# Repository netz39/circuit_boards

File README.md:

Circuit Boards
==============

Various PCBs without own projects. In fact these are some circuit boards for various uses but without the usual project stuff around, just the schematics and board files and the basic stuff to get it running, that's it.

Each project is in a subfolder and has its own LICENSE and README files. If you want more information about a project, see those files.

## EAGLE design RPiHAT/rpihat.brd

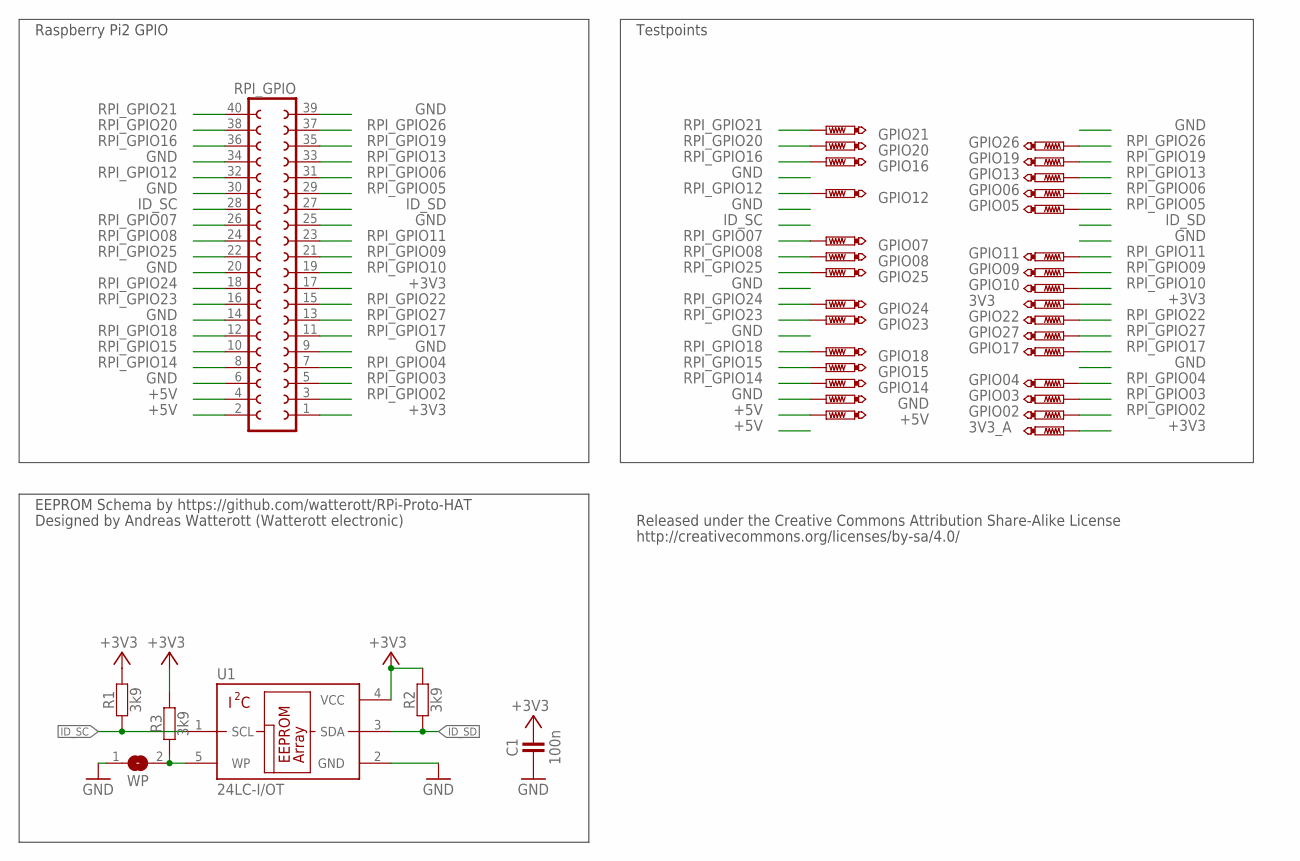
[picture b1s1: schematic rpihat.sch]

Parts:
3V3, 3V3_A: +3.3V; TP06R
+5V: PTR1TP06R; TP06R
C1: 100n; R0603
GND: PTR1TP06R; TP06R
GPIO02, GPIO03, GPIO04, GPIO05, GPIO06, GPIO07, GPIO08, GPIO09, GPIO10, GPIO11, GPIO12, GPIO13, GPIO14, GPIO15, GPIO16, GPIO17, GPIO18, GPIO19, GPIO20, GPIO21, GPIO22, GPIO23, GPIO24, GPIO25, GPIO26, GPIO27: PTR1TP06R; TP06R
R1, R2, R3: 3k9; R0603
RPI_GPIO: FE20-2
U1: 24LC-I/OT; SOT23-5
WP: JUMPER2-NOCREAM; JUMPER2_NC

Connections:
+3V3: 3V3.TP, 3V3_A.TP, C1.2, R1.2, R2.2, R3.2, RPI_GPIO.1, RPI_GPIO.17, U1.4 (VCC)
+5V: +5V.TP, RPI_GPIO.2, RPI_GPIO.4
GND: C1.1, GND.TP, RPI_GPIO.6, RPI_GPIO.9, RPI_GPIO.14, RPI_GPIO.20, RPI_GPIO.25, RPI_GPIO.30, RPI_GPIO.34, RPI_GPIO.39, U1.2 (GND), WP.1
ID_SC: R1.1, RPI_GPIO.28, U1.1 (SCL)
ID_SD: R2.1, RPI_GPIO.27, U1.3 (SDA)
RPI_GPIO02: GPIO02.TP, RPI_GPIO.3
RPI_GPIO03: GPIO03.TP, RPI_GPIO.5
RPI_GPIO04: GPIO04.TP, RPI_GPIO.7
RPI_GPIO05: GPIO05.TP, RPI_GPIO.29
RPI_GPIO06: GPIO06.TP, RPI_GPIO.31
RPI_GPIO07: GPIO07.TP, RPI_GPIO.26
RPI_GPIO08: GPIO08.TP, RPI_GPIO.24
RPI_GPIO09: GPIO09.TP, RPI_GPIO.21
RPI_GPIO10: GPIO10.TP, RPI_GPIO.19
RPI_GPIO11: GPIO11.TP, RPI_GPIO.23
RPI_GPIO12: GPIO12.TP, RPI_GPIO.32
RPI_GPIO13: GPIO13.TP, RPI_GPIO.33
RPI_GPIO14: GPIO14.TP, RPI_GPIO.8
RPI_GPIO15: GPIO15.TP, RPI_GPIO.10
RPI_GPIO16: GPIO16.TP, RPI_GPIO.36
RPI_GPIO17: GPIO17.TP, RPI_GPIO.11
RPI_GPIO18: GPIO18.TP, RPI_GPIO.12
RPI_GPIO19: GPIO19.TP, RPI_GPIO.35
RPI_GPIO20: GPIO20.TP, RPI_GPIO.38
RPI_GPIO21: GPIO21.TP, RPI_GPIO.40
RPI_GPIO22: GPIO22.TP, RPI_GPIO.15
RPI_GPIO23: GPIO23.TP, RPI_GPIO.16
RPI_GPIO24: GPIO24.TP, RPI_GPIO.18
RPI_GPIO25: GPIO25.TP, RPI_GPIO.22
RPI_GPIO26: GPIO26.TP, RPI_GPIO.37
RPI_GPIO27: GPIO27.TP, RPI_GPIO.13
WP: R3.1, U1.5 (WP), WP.2

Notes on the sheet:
EEPROM Schema by https://github.com/watterott/RPi-Proto-HAT
Raspberry Pi2 GPIO
Testpoints
Designed by Andreas Watterott (Watterott electronic)
http://creativecommons.org/licenses/by-sa/4.0/
Released under the Creative Commons Attribution Share-Alike License

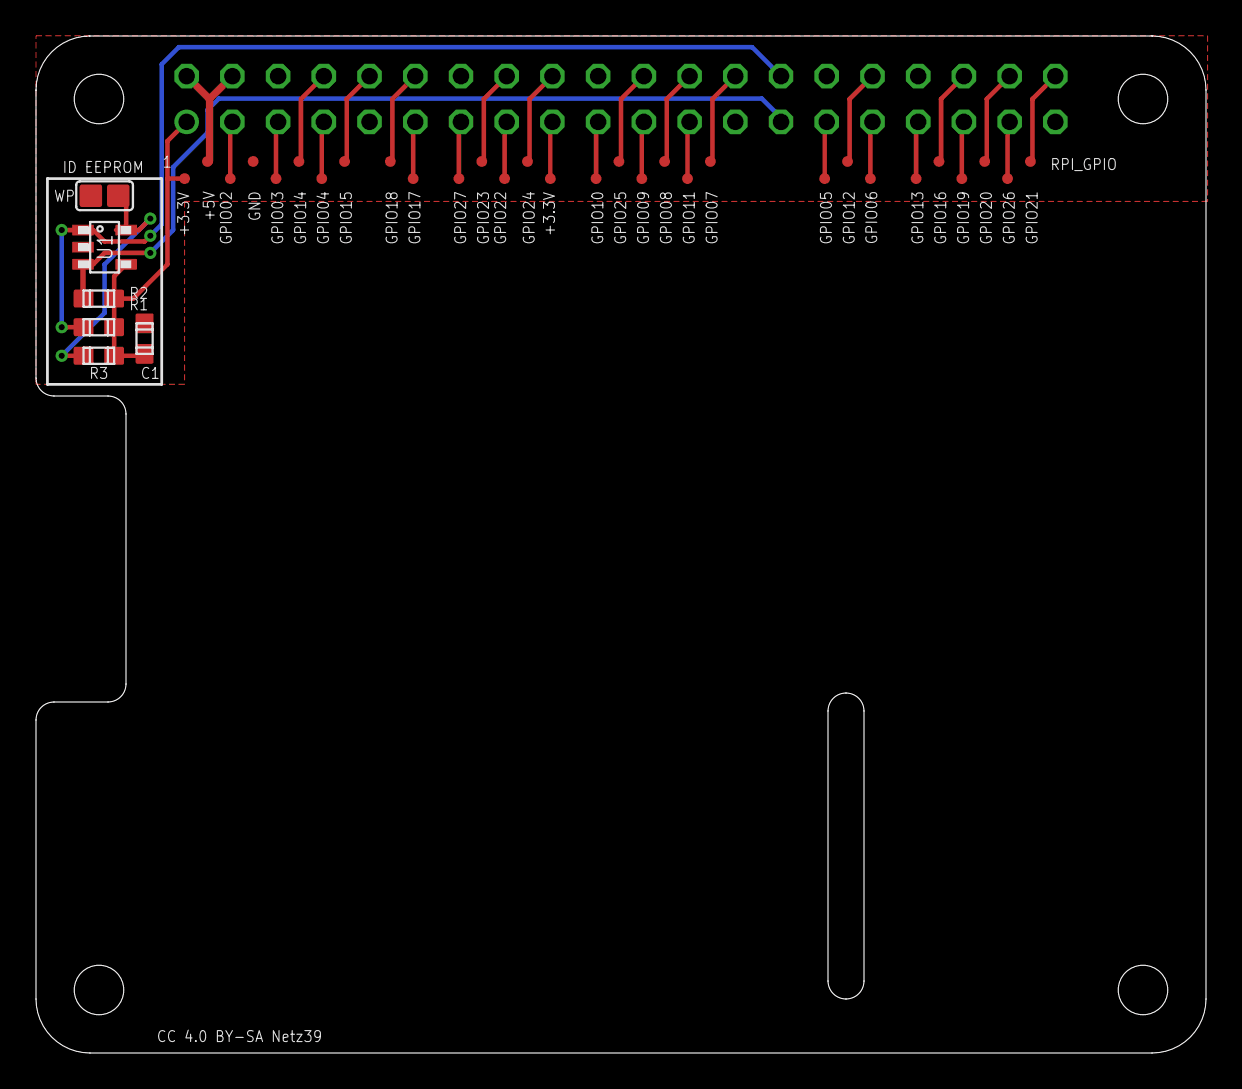
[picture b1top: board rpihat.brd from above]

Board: 2 copper layers, 65.0 x 56.5 mm, 37 parts (1 on the bottom side), 32 nets.

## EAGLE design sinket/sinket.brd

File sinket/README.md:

The [Trinket](http://learn.adafruit.com/introducing-trinket) by adafruit
is an awesome small board based on an Atmel ATtiny85 microcontroller.
Although just a little less than 8$ or 8€ we made a clone for ourselves
which is not that small but a single layer PCB design for easy
manufacturing in your local hackerspace, of course 100% compatible on
the electrical side. You can use all the software, tutorials and so on.
The parts are easily available in Europe or just right already there in
your part storage.

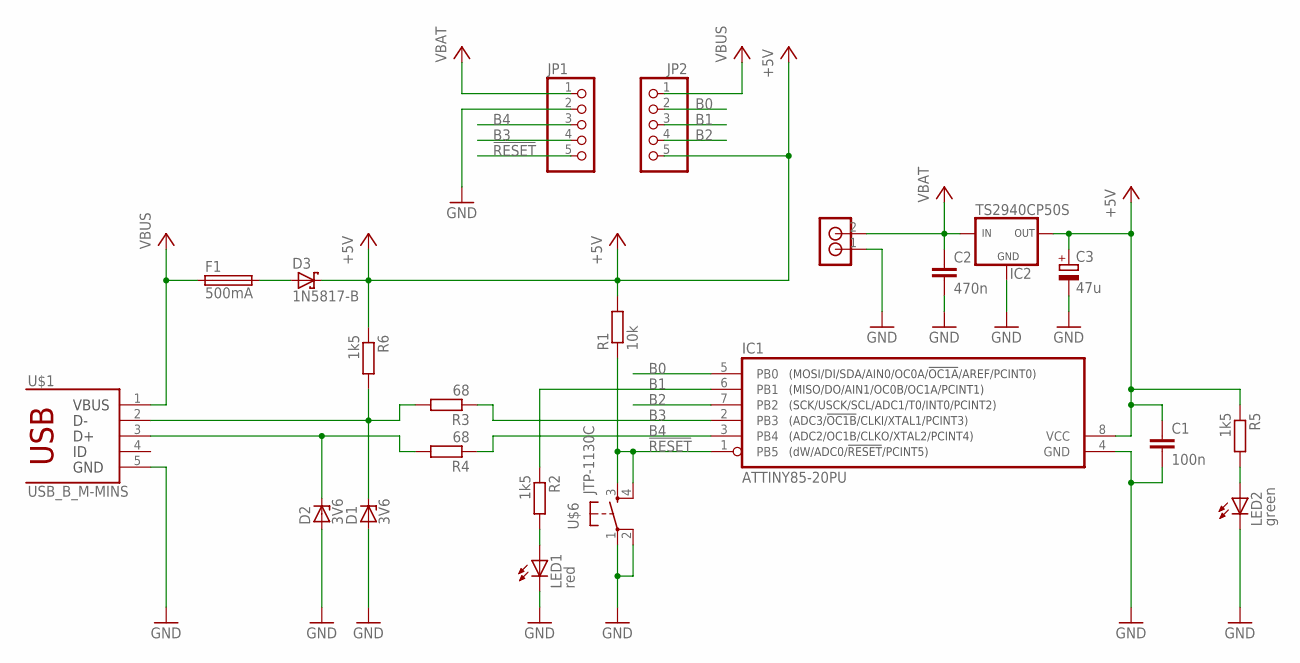
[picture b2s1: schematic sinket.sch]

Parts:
C1: 100n; C1206
C2: 470n; C025-030X050
C3: 47u; E2,5-6
D1, D2: 3V6; SOD80C
D3: 1N5817-B; DO41-7.6
F1: 500mA; LP60-050
IC1: ATTINY85-20PU; 8P3
IC2: TS2940CP50S; TO-252
JP1, JP2: PINHD-1X5; 1X05
LED1: red; LED5MM
LED2: green; LED5MM
R1: 10k; R1206
R2, R5, R6: 1k5; R1206
R3, R4: 68; R1206
U$1: USB_B_M-MINS; LUMBERG_2486-01
U$6: JTP-1130C; JTP-1130
U$7: RIACON_101_2

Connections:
!RESET: IC1.1 (PB5), JP1.5, R1.1, U$6.3 (S), U$6.4 (S1)
+5V: C1.1, C3.+, D3.C, IC1.8 (VCC), IC2.3 (OUT), JP2.5, R1.2, R5.1, R6.1
B0: IC1.5 (PB0), JP2.2
B1: IC1.6 (PB1), JP2.3, R2.1
B2: IC1.7 (PB2), JP2.4
B3: IC1.2 (PB3), JP1.4, R3.1
B4: IC1.3 (PB4), JP1.3, R4.1
GND: C1.2, C2.2, C3.-, D1.A, D2.A, IC1.4 (GND), IC2.2 (GND), JP1.2, LED1.K (C), LED2.K (C), U$1.5, U$6.1, U$6.2 (P1), U$7.1
unnamed: D1.C, R3.2, R6.2, U$1.2
unnamed: D3.A, F1.P$2 (2)
unnamed: D2.C, R4.2, U$1.3
unnamed: LED1.A, R2.2
unnamed: LED2.A, R5.2
VBAT: C2.1, IC2.1 (IN), JP1.1, U$7.2
VBUS: F1.P$1 (1), JP2.1, U$1.1

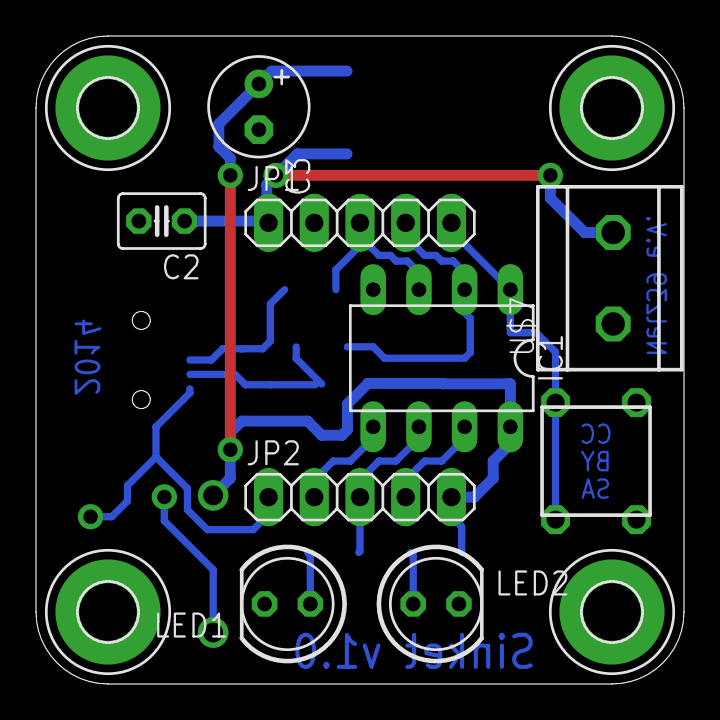
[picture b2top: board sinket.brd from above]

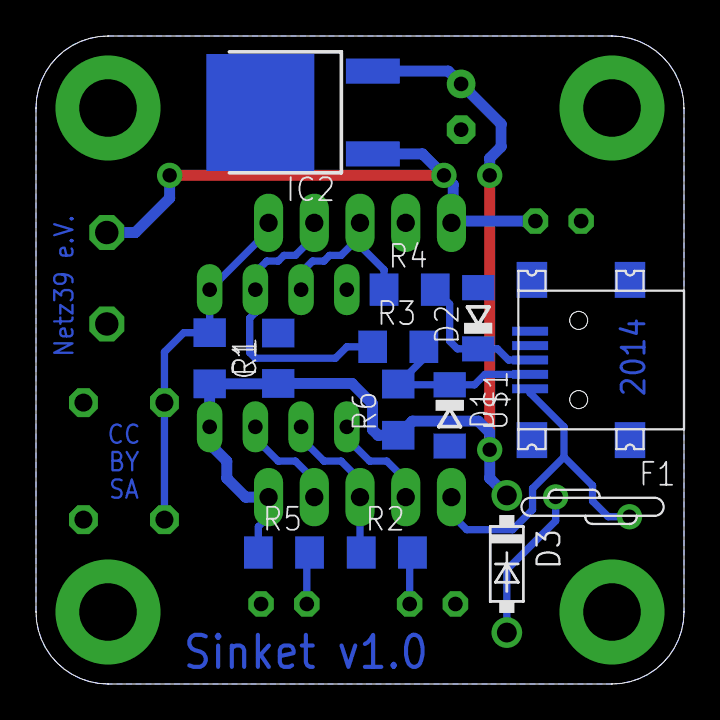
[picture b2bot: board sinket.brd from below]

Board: 2 copper layers, 36.0 x 36.0 mm, 26 parts (13 on the bottom side), 15 nets.

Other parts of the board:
U$2, U$3, U$4, U$5: 3,2-PAD

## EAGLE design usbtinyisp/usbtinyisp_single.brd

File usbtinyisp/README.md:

This is the circuit and layout for an AVR programmer and SPI interface. It's based on USBtinyISP from [adafruit](http://learn.adafruit.com/usbtinyisp) and you should flash their firmware, because it's also using their USB id. ;-)

However this is a single layer PCB with another form factor. We made this in our Hackerspace [Netz39](http://www.netz39.de/) for the AVR101 and other courses people can attend there.

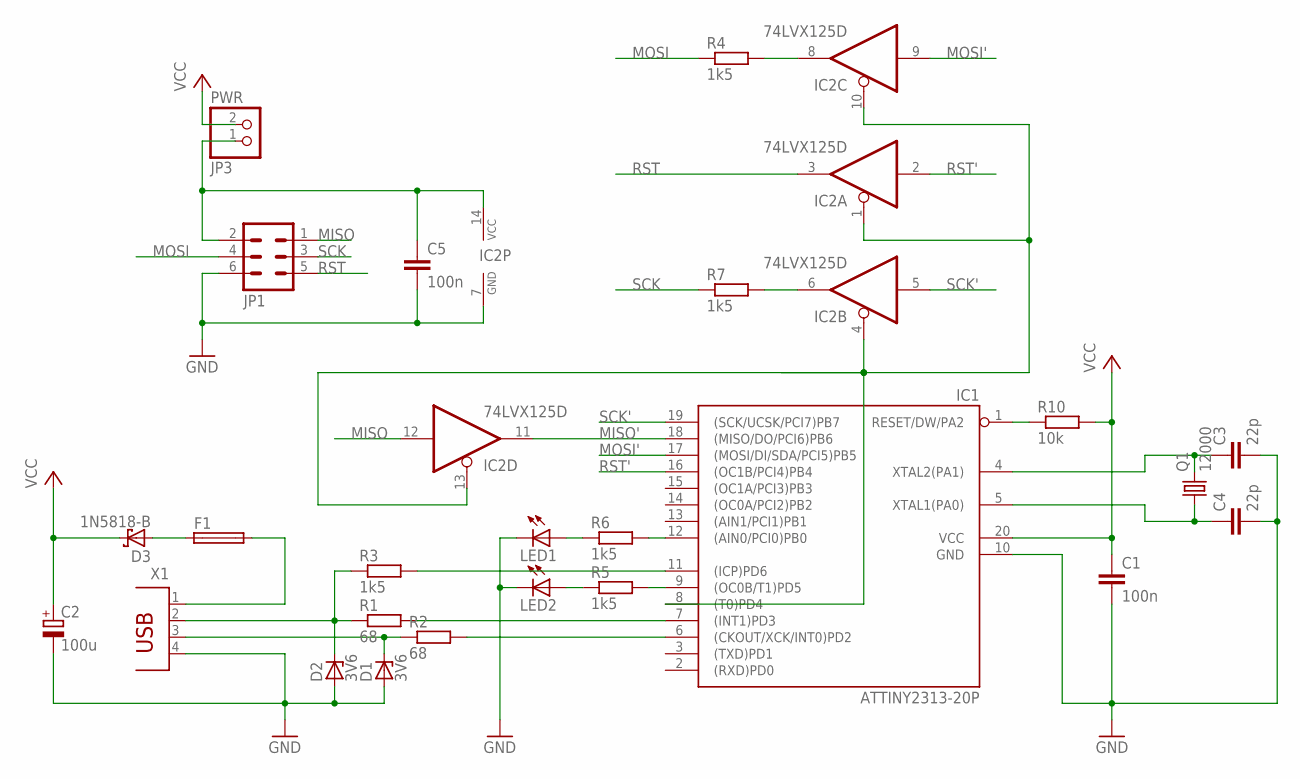
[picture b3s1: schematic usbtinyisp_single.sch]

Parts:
C1, C5: 100n; C0805
C2: 100u; E2,5-6
C3, C4: 22p; C1206
D1, D2: 3V6; SOD80C
D3: 1N5818-B; DO41-7.6
F1: PTC-FUSE-LP60-050; LP60-050
IC1: ATTINY2313-20P; DIL20
IC2: 74LVX125D; SO14
JP1: ML6
JP3: PWR; 1X02
LED1, LED2: LED3MM
Q1: 12000; HC49U-V
R1, R2: 68; 0207/10
R3, R4, R5, R6: 1k5; R0805
R7: 1k5; 0207/10
R10: 10k; R0805
X1: PN61729

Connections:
GND: C1.2, C2.-, C3.2, C4.2, C5.2, D1.A, D2.A, IC1.10 (GND), IC2.7 (GND), JP1.6, LED1.K (C), LED2.K (C), X1.4
MISO: IC2.12 (I), JP1.1
MISO': IC1.18 ((MISO/DO/PCI6)PB6), IC2.11 (O)
MOSI: JP1.4, R4.1
MOSI': IC1.17 ((MOSI/DI/SDA/PCI5)PB5), IC2.9 (I)
unnamed: D2.C, R1.1, R3.1, X1.2
unnamed: D1.C, R2.1, X1.3
unnamed: IC1.7 ((INT1)PD3), R1.2
unnamed: LED1.A, R6.1
unnamed: IC1.6 ((CKOUT/XCK/INT0)PD2), R2.2
unnamed: IC1.12 ((AIN0/PCI0)PB0), R6.2
unnamed: IC1.1 (RESET/DW/PA2), R10.1
unnamed: IC1.9 ((OC0B/T1)PD5), R5.2
unnamed: LED2.A, R5.1
unnamed: IC2.6 (O), R7.2
unnamed: IC2.8 (O), R4.2
unnamed: D3.A, F1.P$1 (1)
unnamed: IC1.8 ((T0)PD4), IC2.1 (OE), IC2.4 (OE), IC2.10 (OE), IC2.13 (OE)
unnamed: IC1.11 ((ICP)PD6), R3.2
RST: IC2.3 (O), JP1.5
RST': IC1.16 ((OC1B/PCI4)PB4), IC2.2 (I)
SCK: JP1.3, R7.1
SCK': IC1.19 ((SCK/UCSK/PCI7)PB7), IC2.5 (I)
VBUS: F1.P$2 (2), X1.1
VCC: C1.1, C2.+, D3.C, IC1.20 (VCC), JP3.2, R10.2
VTARGET: C5.1, IC2.14 (VCC), JP1.2, JP3.1
XTAL1: C4.1, IC1.5 (XTAL1(PA0)), Q1.1
XTAL2: C3.1, IC1.4 (XTAL2(PA1)), Q1.2

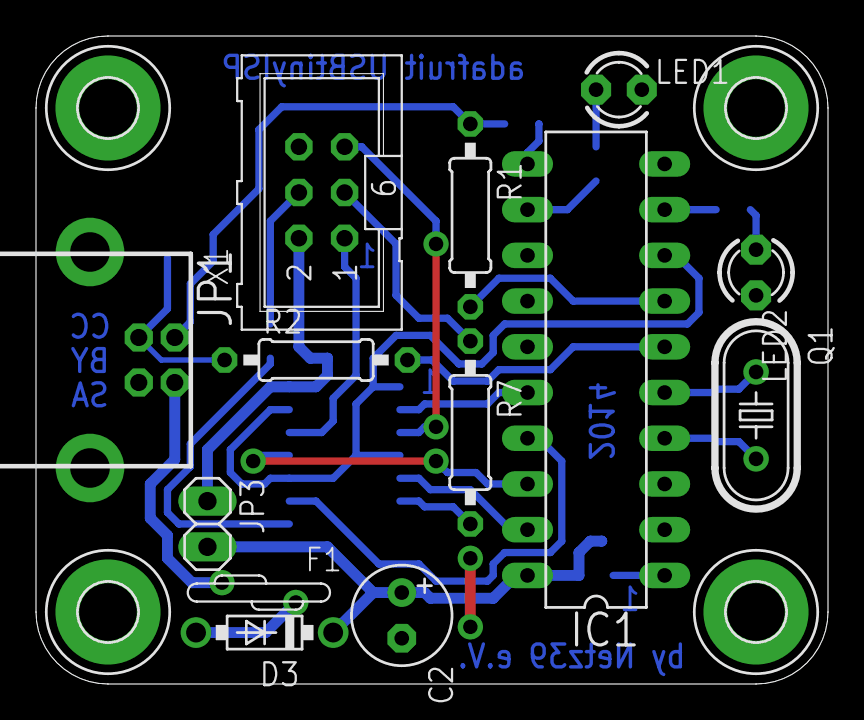
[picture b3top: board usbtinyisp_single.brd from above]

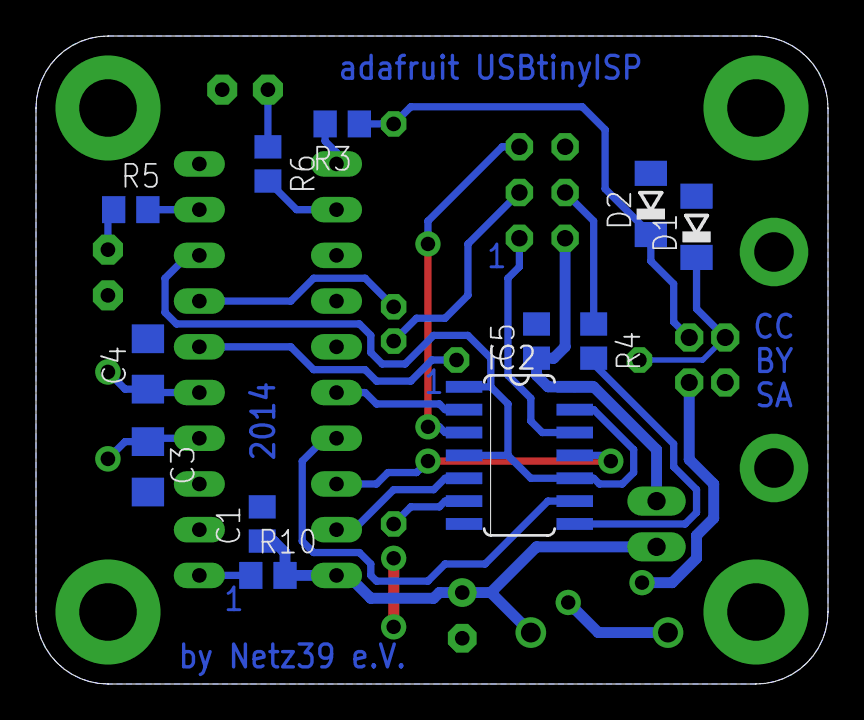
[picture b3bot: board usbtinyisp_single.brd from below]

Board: 2 copper layers, 44.0 x 36.0 mm, 29 parts (12 on the bottom side), 28 nets.

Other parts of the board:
U$1, U$2, U$3, U$4: 3,2-PAD

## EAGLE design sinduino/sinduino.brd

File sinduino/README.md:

This is yet another [Arduino](http://arduino.cc/) clone. It's based on the [Paperduino Leonardo](http://txapuzas.blogspot.de/2009/12/paperduino-leonardo-clon-de-arduino.html), but it's called *sinduino*. The name comes from the purpose of this board to create a single layer Arduino clone and the usual "duino".

As said above we want a single layer PCB to be able to etch it without all the problems a dual layer etching at home has. There are single layer Arduino boards out there, but none of them has USB. To simplify the design and staying low cost we wanted to use the ATmega32U4 with integrated USB which is the one used on the Arduino Leonardo, too.

However there are some trade offs. The most important one: this is not pin compatible to the well known Arduino and its shields

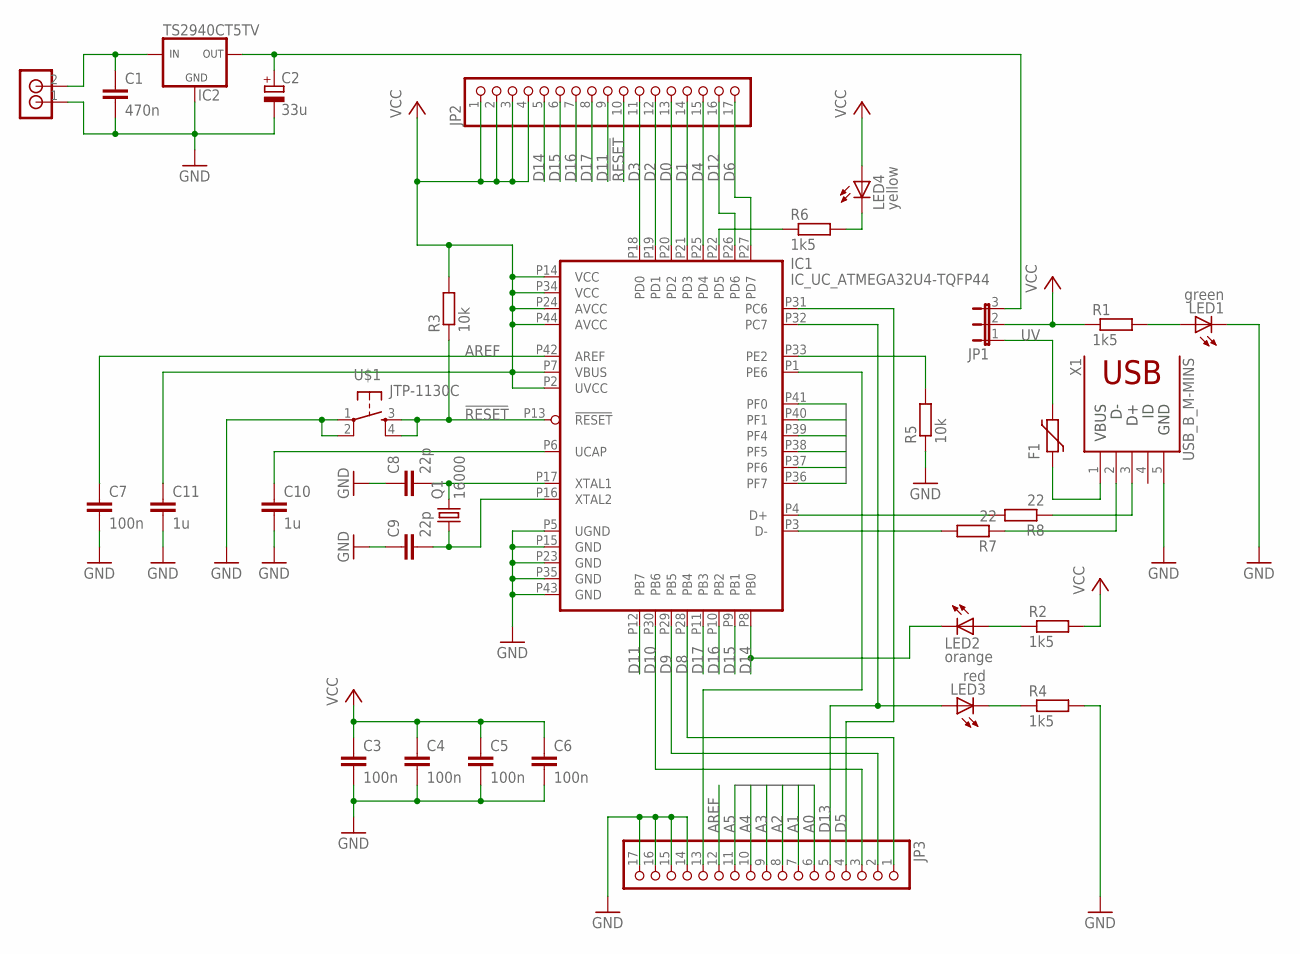
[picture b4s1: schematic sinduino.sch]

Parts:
C1: 470n; C025-025X050
C2: 33u; E2,5-5
C3, C4, C5, C6, C7: 100n; C1206
C8, C9: 22p; C1206
C10, C11: 1u; C1206
F1: FUSE_PTC-1812; PTC1812L
IC1: IC_UC_ATMEGA32U4-TQFP44; TQFP-44
IC2: TS2940CT5TV; TO220V
JP1: JP2E; JP2
JP2, JP3: PINHD-1X17; 1X17
LED1: green; LED3MM
LED2: orange; LED3MM
LED3: red; LED3MM
LED4: yellow; LED3MM
Q1: 16000; HC49U-V
R1, R2, R4, R6: 1k5; R1206
R3, R5: 10k; R1206
R7, R8: 22; R1206
U$1: JTP-1130C; JTP-1130
U$3: RIACON_101_2
X1: USB_B_M-MINS; LUMBERG_2486-01

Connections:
!RESET: IC1.P13 (!RESET), JP2.10, R3.1, U$1.3 (S), U$1.4 (S1)
A0: IC1.P36 (PF7), JP3.6
A1: IC1.P37 (PF6), JP3.7
A2: IC1.P38 (PF5), JP3.8
A3: IC1.P39 (PF4), JP3.9
A4: IC1.P40 (PF1), JP3.10
A5: IC1.P41 (PF0), JP3.11
AREF: C7.1, IC1.P42 (AREF), JP3.12
D0: IC1.P20 (PD2), JP2.13
D1: IC1.P21 (PD3), JP2.14
D2: IC1.P19 (PD1), JP2.12
D3: IC1.P18 (PD0), JP2.11
D4: IC1.P25 (PD4), JP2.15
D5: IC1.P31 (PC6), JP3.4
D6: IC1.P27 (PD7), JP2.17
D7: IC1.P1 (PE6), JP3.13
D8: IC1.P28 (PB4), JP3.1
D9: IC1.P29 (PB5), JP3.2
D10: IC1.P30 (PB6), JP3.3
D11: IC1.P12 (PB7), JP2.9
D12: IC1.P26 (PD6), JP2.16
D13: IC1.P32 (PC7), JP3.5, LED3.A
D14: IC1.P8 (PB0), JP2.5, LED2.K (C)
D15: IC1.P9 (PB1), JP2.6
D16: IC1.P10 (PB2), JP2.7
D17: IC1.P11 (PB3), JP2.8
D+: IC1.P4 (D+), R8.2
D-: IC1.P3 (D-), R7.2
GND: C1.2, C2.-, C3.2, C4.2, C5.2, C6.2, C7.2, C8.1, C9.1, C10.2, C11.2, IC1.P5 (UGND), IC1.P15 (GND), IC1.P23 (GND), IC1.P35 (GND), IC1.P43 (GND), IC2.2 (GND), JP3.14, JP3.15, JP3.16, JP3.17, LED1.K (C), R4.2, R5.1, U$1.1, U$1.2 (P1), U$3.1, X1.5
HWB: IC1.P33 (PE2), R5.2
unnamed: R7.1, X1.2
unnamed: R8.1, X1.3
unnamed: F1.1, X1.1
unnamed: LED4.K (C), R6.2
unnamed: LED1.A, R1.2
unnamed: C1.1, IC2.1 (IN), U$3.2
unnamed: C2.+, IC2.3 (OUT), JP1.3
unnamed: LED2.A, R2.1
unnamed: LED3.K (C), R4.1
TXLED: IC1.P22 (PD5), R6.1
UCAP: C10.1, IC1.P6 (UCAP)
UV: F1.2, JP1.1
VCC: C3.1, C4.1, C5.1, C6.1, C11.1, IC1.P2 (UVCC), IC1.P7 (VBUS), IC1.P14 (VCC), IC1.P24 (AVCC), IC1.P34 (VCC), IC1.P44 (AVCC), JP1.2, JP2.1, JP2.2, JP2.3, JP2.4, LED4.A, R1.1, R2.2, R3.2
XTAL1: C8.2, IC1.P17 (XTAL1), Q1.2
XTAL2: C9.2, IC1.P16 (XTAL2), Q1.1

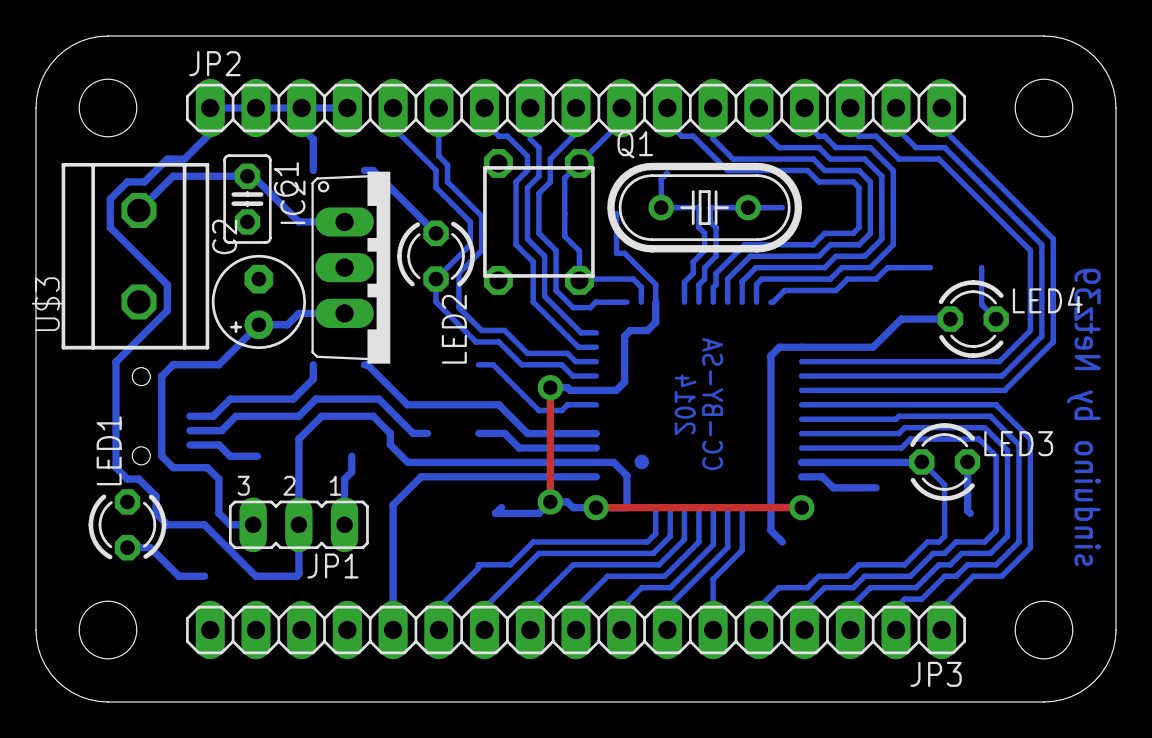
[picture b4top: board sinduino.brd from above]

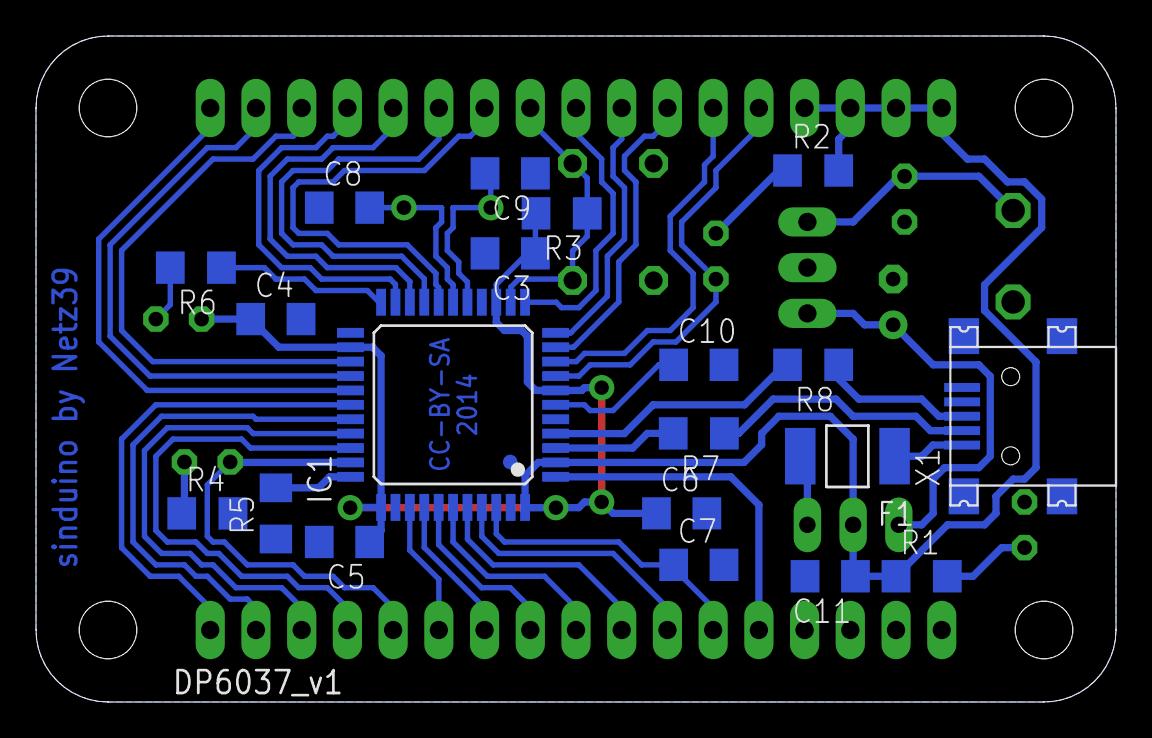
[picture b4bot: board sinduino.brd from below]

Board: 2 copper layers, 60.0 x 37.0 mm, 34 parts (20 on the bottom side), 45 nets.

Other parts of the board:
U$2: DP6037_V1

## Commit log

2014-01-10 add old v2.0 from adafruit
2014-01-10 started reworking for single layer board
2014-01-10 update dimensions and change some packages
2014-01-10 unsmash
2014-01-13 vergessene Änderungen
    wenn man nicht alles gleich commited :-/
2014-01-13 move mounting holes inward
2014-01-13 replace mounting pads
2014-01-13 swapped some gates and moved all parts around
2014-01-14 routed
    ready for soldering (first test)
2014-01-14 add text, license, and readme
2014-01-14 swap LED1 with resistor
2014-01-16 import sinduino last state
    based on [Paperduino
    Leonardo](http://txapuzas.blogspot.de/2009/12/paperduino-leonardo-clon-de-arduino.html)
2014-01-16 add license and readme
2014-01-16 proceed connecting
2014-01-17 add git ignore list
2014-01-17 almost connected everything
2014-01-18 complete schematic and start routing
2014-01-19 proceed routing, move uC, start over …
2014-01-19 switched one led with its resistor
2014-01-19 proceed routing
2014-01-19 route lower right part
2014-01-20 route left part of the board
2014-01-20 move some things around in the upper right
2014-01-20 routed all the stuff around the xtal
2014-01-20 routing complete
2014-01-20 dimension
2014-01-20 added text
2014-01-21 name some unnamed signals
    and improve xtal routing
2014-01-22 adapt resistor values and move one via
2014-02-17 replace mini usb connector and fix #3
2014-02-20 change XTAL capicator values to 22p (you can not buy 18p)
2014-02-28 move vias for round wire lengths
    replace elko package
2014-02-28 update parts from libraries
2014-03-06 add fuse and diode and route again the whole board
2014-03-07 changed board size to 36×36
2014-03-07 start placing parts
2014-03-07 started working on sinket
2014-03-07 replace uC with new ATtiny25 device package symbol
2014-03-07 proceed schematics (stopped because a schottky diode is missing)
2014-03-07 add remaining parts to schematic
2014-03-07 sinket: add fuse
2014-03-07 change fuse package
2014-03-12 replace all 0805 parts with 1206 and start routing
2014-03-12 finish routing
2014-03-12 did DRC, added text and space for logo
2014-04-18 LED package changed, Schraubklemme added, parts moved
2014-04-18 move fuse away from mounting hole
2015-11-24 Dimensions DXF for minimal HAT
    The drawing is based on the RPi B+ HAT specification, see
    https://github.com/raspberrypi/hats
2015-11-26 RPiHat: Schematics and Board Layout
    I2C memory schematics from https://github.com/watterott/RPi-Proto-HAT
2015-11-26 Licensing
    added License for the EEPROM design and CC4.0 BY-SA for Netz39 to the board.
2015-11-27 RPi HAT: changed all wires to 10 mil minimum
    3.3V wire also changed to 10 mil, as there will be a max current of 50 mA.
2015-11-27 RPi HAT: Documentation
2015-11-27 RPi HAT: Ground Planes
    * Adjusted the top ground plane
    * Added kongruent bottom ground plane
2015-12-12 RPi HAT: Center traces between connector pins.

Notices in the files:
sinduino/sinduino.brd:
CC-BY-SA
